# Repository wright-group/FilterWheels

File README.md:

# FilterWheels

Electronics and harware used to automate the process of moving optical filter wheels during experiments.

See documentation.pdf for full information.

## yaq support

The daemons in this repository (`./wright-filter-wheels`) in outdated and unmaintained; instead, use the wright-stepper-motor-box kind found in [`yaqd-wright`](https://github.com/wright-group/yaqd-wright).

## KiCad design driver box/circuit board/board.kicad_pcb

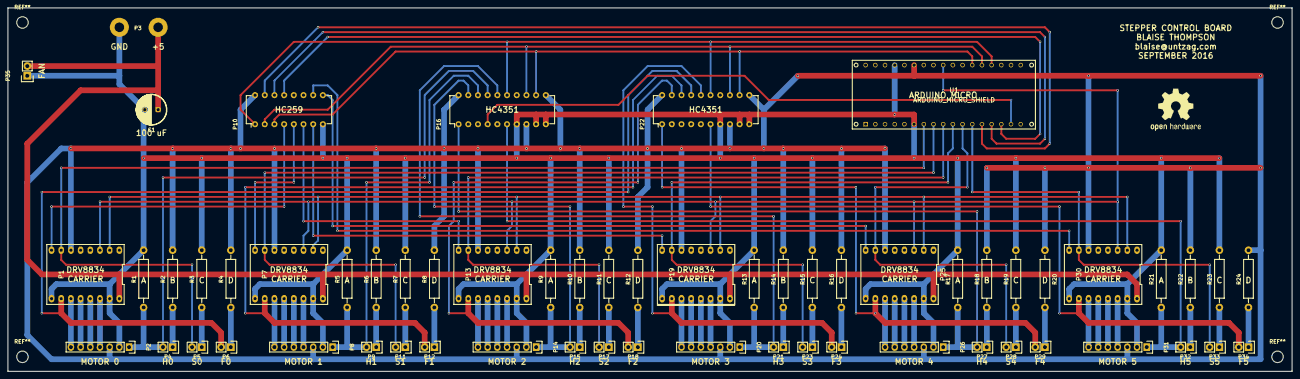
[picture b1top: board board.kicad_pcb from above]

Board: 2 copper layers, 336.6 x 95.2 mm, 61 parts (0 on the bottom side), 79 nets.

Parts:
C1: CP1; C_Radial_D8_L11.5_P3.5
P1: DRIVER 0; driver
P2, P8, P14, P20, P26, P31: DB9; Pin_Header_Straight_1x07
P3: POWER; WireConnection_2.50mmDrill
P4, P9, P15, P21, P27, P32: LED H; Socket_Strip_Straight_1x02
P5, P11, P17, P23, P28, P33: LED S; Socket_Strip_Straight_1x02
P6, P12, P18, P24, P29, P34: LED F; Socket_Strip_Straight_1x02
P7: DRIVER 1; driver
P10: HC259; DIP-16_W7.62mm
P13: DRIVER 2; driver
P16, P22: HC4351; DIP-20_W7.62mm
P19: DRIVER 3; driver
P25: DRIVER 4; driver
P30: DRIVER 5; driver
P35: FAN; Socket_Strip_Straight_1x02
R1, R2, R3, R4, R5, R6, R7, R8, R9, R10, R11, R12, R13, R14, R15, R16, R17, R18, R19, R20, R21, R22, R23, R24: R; Resistor_Horizontal_RM15mm
U1: ARDUINO_MICRO_SHIELD

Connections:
/0: P1.2, P7.2, P13.2, P19.2, P25.2, P30.2, U1.A4
/1: P1.3, P7.3, P13.3, P19.3, P25.3, P30.3, U1.A5
/5: P1.6, P2.3, P7.6, P8.3, P10.16, P13.6, P14.3, P16.8, P16.11, P16.20, P19.6, P20.3, P22.8, P22.11, P22.20, P25.6, P26.3, P30.6, P31.3, R2.1, R4.1, R6.1, R8.1, R10.1, R12.1, R14.1, R16.1, R18.1, R20.1, R22.1, R24.1, U1.5V
/D0: P1.8, P10.4
/D1: P7.8, P10.5
/D2: P10.6, P13.8
/D3: P10.7, P19.8
/D4: P10.9, P25.8
/D5: P10.10, P30.8
/F0: P1.10, P6.2, P22.17
/F1: P7.10, P12.2, P22.18
/F2: P13.10, P18.2, P22.19
/F3: P19.10, P22.16, P24.2
/F4: P22.1, P25.10, P29.2
/F5: P22.6, P30.10, P34.2
/G: C1.2, P1.9, P1.15, P2.2, P3.1, P7.9, P7.15, P8.2, P10.8, P13.9, P13.15, P14.2, P16.7, P16.9, P16.10, P19.9, P19.15, P20.2, P22.7, P22.9, P22.10, P25.9, P25.15, P26.2, P30.9, P30.15, P31.2, P35.1, R1.1, R3.1, R5.1, R7.1, R9.1, R11.1, R13.1, R15.1, R17.1, R19.1, R21.1, R23.1, U1.GND
/H0: P2.1, P4.2, P16.17, R1.2
/H1: P8.1, P9.2, P16.18, R5.2
/H2: P14.1, P15.2, P16.19, R9.2
/H3: P16.16, P20.1, P21.2, R13.2
/H4: P16.1, P26.1, P27.2, R17.2
/H5: P16.6, P31.1, P32.2, R21.2
/S0: P1.7, P5.2, U1.2
/S1: P7.7, P11.2, U1.3
/S2: P13.7, P17.2, U1.4
/S3: P19.7, P23.2, U1.5
/S4: P25.7, P28.2, U1.6
/S5: P30.7, P33.2, U1.7
/V: C1.1, P1.16, P3.2, P7.16, P13.16, P19.16, P25.16, P30.16, P35.2
unnamed: P1.11, P2.7
unnamed: P1.12, P2.6
unnamed: P1.13, P2.5
unnamed: P1.14, P2.4
unnamed: P4.1, R2.2
unnamed: P5.1, R3.2
unnamed: P6.1, R4.2
unnamed: P7.11, P8.7
unnamed: P7.12, P8.6
unnamed: P7.13, P8.5
unnamed: P7.14, P8.4
unnamed: P9.1, R6.2
unnamed: P10.1, P16.15, P22.15, U1.A0
unnamed: P10.2, P16.13, P22.13, U1.A1
unnamed: P10.3, P16.12, P22.12, U1.A2
unnamed: P10.13, U1.10
unnamed: P10.14, U1.9
unnamed: P10.15, U1.8
unnamed: P11.1, R7.2
unnamed: P12.1, R8.2
unnamed: P13.11, P14.7
unnamed: P13.12, P14.6
unnamed: P13.13, P14.5
unnamed: P13.14, P14.4
unnamed: P15.1, R10.2
unnamed: P16.4, U1.11
unnamed: P17.1, R11.2
unnamed: P18.1, R12.2
unnamed: P19.11, P20.7
unnamed: P19.12, P20.6
unnamed: P19.13, P20.5
unnamed: P19.14, P20.4
unnamed: P21.1, R14.2
unnamed: P22.4, U1.12
unnamed: P23.1, R15.2
unnamed: P24.1, R16.2
unnamed: P25.11, P26.7
unnamed: P25.12, P26.6
unnamed: P25.13, P26.5
unnamed: P25.14, P26.4
unnamed: P27.1, R18.2
unnamed: P28.1, R19.2
unnamed: P29.1, R20.2
unnamed: P30.11, P31.7
unnamed: P30.12, P31.6
unnamed: P30.13, P31.5
unnamed: P30.14, P31.4
unnamed: P32.1, R22.2
unnamed: P33.1, R23.2
unnamed: P34.1, R24.2

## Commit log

2016-10-11 add circuit board, firmware, license
    version 0.0.0
    - add circuit board
    - add firmware
    - add gitignore
    - some content for README
    - added LICENSE (CERN Open Hardware Licence v1.2)
2016-10-13 firmware complete
    version 0.1.0
    - firmware now supports simultanious motor motion
    - firmware now supports directional motion
    - firmware now supports queries (including faults)
    - firmware now supports microstepping
    - added pins and cables records
2016-10-13 documentation
    no version change
2016-10-13 termination implementation
    version 0.1.1
    - termination is now explicitly accounted for
    - fixed bugs in reading faults
    - prettified firmware
2016-10-20 add mechanical drawings
    version 0.2.0
    -added Inventor files and pdf for all machined, mechanical components
2020-06-08 first major commit, is-serial added, WIP, verify dir struct, untested except for test_script
2020-06-08 added script for testing
2020-06-09 added microsteps and microint code, WIP
2020-06-09 modified folders and yaqd names
2020-06-09 added extra Q,H motor_num, changed microstep function
2020-06-09 additional adjustment of code, procedure for last line of _home needs changing as _destination is NULLed currently and get_position is NULLed
2020-06-10 changed _set_position code to reflect absolute not relative position change, added home to init, made sure _position was written to, suggest state.toml to save positions and read from at start
2020-06-16 WIP: changed dir structure, adding identifier test code, current fail at toml.load
2020-06-16 mergeable, tested, get_units, set_relative, get_destination not populated
2020-06-17 changes made per reviewer v1 (incomplete)
2020-06-17 rev 2
2020-06-17 WIP pip install error diagnosing
2020-06-17 tested with offset removed for now, no set_relative as yet
2021-11-16 WIP adding extra home feature for UL
2026-01-18 main loop: delay -> mllis
2026-01-18 issue #2
2026-01-18 less digital writes
    only call `setSelect` when we have something to do
2026-01-18 cleanup
2026-01-21 safe for millis overflow
2026-01-21 add meta
2026-01-21 firmware: reduce serial latency (#5)
    * main loop: delay -> mllis
    * issue #2
    * Update firmware.ino
    * less digital writes
    only call `setSelect` when we have something to do
    * cleanup
2026-01-23 more care with multiplexers
    take time writing direction, reading home
2026-01-26 reproducible homing
2026-01-26 remove debug serial comms
2026-01-27 bugfixes
    consolidate wait times to be only function of ms_step
    some doc additions
